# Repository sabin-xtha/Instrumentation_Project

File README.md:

# Self Balancing Robot

This repo is for the details of the self balancing robot created from scratch.
This repo uses MPU6050 as the IMU(Intertial Measurement Unit). Data from the MPU is read using the [i2cdevlib and MPU6050](https://github.com/jrowberg/i2cdevlib).
Both library are added to the libraryfiles diretory which can be copied to the Arduino library inorder to use it in the program.

Inorder to test if the motor works with driver or not uncomment the code in  which will run the motor in one direction only.

This is the Instrumentation Course Project done by second year Electronics, Communication and Information Engineering Students from IOE,Pulchowk Campus.This Repo also contains the Case study documentation required for the same subject related to the Instrumentation based Industries. We did this case study at DDC, Balaju whose report is done at https://www.overleaf.com/project/62e159923e3b4074664e056a .

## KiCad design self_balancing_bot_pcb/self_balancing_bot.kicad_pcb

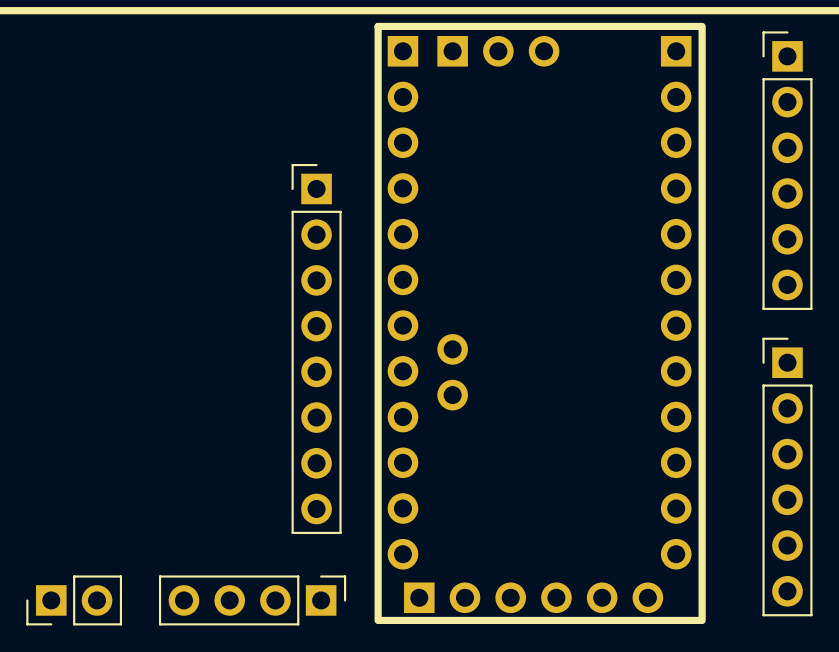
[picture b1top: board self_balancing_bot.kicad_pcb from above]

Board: 2 copper layers, 6 parts (0 on the bottom side), 17 nets, no tracks yet.

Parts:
A1: Arduino_Leonardo; Arduino Pro Mini
J1: Conn_01x08_Female; PinHeader_1x08_P2.54mm_Vertical
J2, J4: Conn_01x06_Female; PinHeader_1x06_P2.54mm_Vertical
J3: Conn_01x04_Female; PinHeader_1x04_P2.54mm_Vertical
J5: Conn_01x02_Female; PinHeader_1x02_P2.54mm_Vertical

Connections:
D11: A1.D11, J4.4
D12: A1.D12, J4.5
D13: A1.D13, J4.6
EN1: A1.D5, J2.6
EN2: A1.D6, J2.1
GND: A1.3 (GND), A1.4 (GND), A1.6 (GND), A1.9 (GND), A1.11 (GND), J1.2, J3.2, J4.2, J5.1
IN1: A1.D4, J2.5
IN2: A1.D7, J2.4
IN3: A1.D8, J2.3
IN4: A1.D9, J2.2
INT: A1.D2, J1.8
RST: A1.7 (RESET), J4.3
RXD: A1.13 (RX1), J3.3
SCL: A1.A5, J1.3
SDA: A1.A4, J1.4
TXD: A1.12 (TX0), J3.4
VCC: A1.2 (VCC), J1.1, J3.1, J4.1, J5.2

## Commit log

2022-08-02 add proteus simuates
2022-08-02 add README.md
2022-08-07 Basic init for Self-Balancing Robot
2022-08-07 minor change
2022-08-10 Read the mpu value using i2devlib library
2022-08-11 wrote a header for running motors
2022-08-11 motor with mpu
2022-08-14 add git ignore
2022-08-14 pcb design kicad
2022-08-14 autosave wala add
2022-08-14 add define.h
2022-08-16 minor changes
2022-08-19 Almost the final code
2023-11-25 update update
